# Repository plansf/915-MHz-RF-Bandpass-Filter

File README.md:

# RF915: 915 MHz LC Filter

I’m developing this as a student RF hardware project: design a compact filter for
the 902–928 MHz band, model it, lay out a PCB, then compare the model with a
NanoVNA measurement. Revision A is the digital prototype, the boards have been simulated, but yet to be fabricated and tested to see comparison of real Vs. theoretical measurements.

I’m keeping the assumptions and current limits visible so the simulation is not mistaken for measured hardware results.

## The design

The filter is a passive, three-resonator LC bandpass network with 50-ohm SMA
ports. It uses 1.8 pF series capacitors, 15 nH series inductors, and a 1.8 nH /
10 pF shunt resonator. The KiCad package includes the filter PCB and a separate
through-reference board. Both are routed as two-layer, 40 x 24 mm boards for a
specified 0.8 mm FR4 stackup.

The Python model calculates S-parameters and can analyze Touchstone 1.x `.s2p`
files. It includes a typical vendor model for the inductors and estimates for
capacitor, trace, connector, and ground-return parasitics. Those PCB and launch
values are assumptions; the design has not had full-wave EM analysis.

## Current results

The simulated board model meets the initial targets in `design.json`:

| Measure | Target | Estimated board model |
|---|---:|---:|
| Insertion loss across 902–928 MHz | ≤ 3 dB | 1.01 dB worst case |
| Return loss across 902–928 MHz | ≥ 10 dB | 25.14 dB worst case |
| Attenuation at 433 MHz | ≥ 15 dB | 30.44 dB |
| Attenuation at 1830 MHz | ≥ 15 dB | 47.65 dB |

These are simulation outputs, not acceptance results. The ideal lumped model
misses the return-loss target, which shows how much the prediction depends on
the estimated PCB parasitics. In an illustrative 300-case sensitivity sweep,
275 cases met the modeled targets; this is not a manufacturing-yield estimate.
See `results/simulation/metrics.json` and `results/simulation/response.png`.

## What has been checked

The original validation run recorded 10 Python tests passing, clean KiCad ERC
and DRC checks for both boards, and valid fabrication exports. These checks cover
the digital design package. The included KiCad reports are the raw ERC/DRC
outputs. No board has been ordered, assembled, or tested with a VNA. The design
also has not had production qualification or full-wave EM analysis.

## Run the model

Python 3.11+ with NumPy and Matplotlib is needed for the analysis scripts. From
this folder in PowerShell:

```powershell
python -m venv .venv
.\.venv\Scripts\python.exe -m pip install -r requirements.txt
.\.venv\Scripts\python.exe rf915.py simulate
```

To analyze a real acquisition, keep the original Touchstone file and complete
`measurements/metadata-template.json` with the instrument and calibration
details. Then run:

```powershell
.\.venv\Scripts\python.exe rf915.py analyze measurements\filter-revA.s2p --kind measured --metadata measurements\filter-revA.json --output results\measured-revA --reference results\simulation\nominal.s2p
```

The analyzer requires complete coverage of the passband and will not label the
included simulated files as measured data. It reports S-parameter metrics, a
comparison plot, CSV data, and group delay.

## Next step: build and measure

The Gerber archives are in `fabrication/`; the parts list is `hardware/BOM.csv`.
Before ordering, confirm the fabricator can provide the specified two-layer,
0.8 mm FR4 stackup. Assemble the filter and through-reference boards, check them
with a multimeter, calibrate the NanoVNA at the cable ends, and save the raw
Touchstone exports and measurement metadata. Compare those measurements with
the model before deciding whether to tune or make Revision B. Do not substitute
1.6 mm board thickness without revising the design.

## Repository map

- `hardware/` — editable KiCad design, BOM, and ERC/DRC records
- `fabrication/` — Gerber, drill, and board ZIP files
- `rf915.py`, `design.json` — model, Touchstone analysis, and design inputs
- `results/simulation/` — simulated Touchstone files, metrics, and plots
- `measurements/` — metadata template and place for future raw measurements
- `tests/` — model and Touchstone parser tests

## References

- [Coilcraft 0603HP SPICE model](https://www.coilcraft.com/getmedia/353e55d2-1d20-470a-9567-550d989b0e5d/spice_0603hp.pdf) — inductor model basis.
- [Amphenol 132134 mechanical drawing](https://www.amphenolrf.com/library/download/link/link_id/593003/parent/132134/) — vertical SMA footprint dimensions.
- [KiCad 9 CLI documentation](https://docs.kicad.org/9.0/en/cli/cli.html) — ERC, DRC, and fabrication export tools.
- [NanoVNA calibration](https://nanovna.com/?page_id=2) and [NanoVNA-Saver](https://github.com/NanoVNA-Saver/nanovna-saver) — instrument setup and Touchstone export references.

The vendor datasheet and KiCad-derived footprints retain their original sources;
they are included as references and are not claimed as original work.

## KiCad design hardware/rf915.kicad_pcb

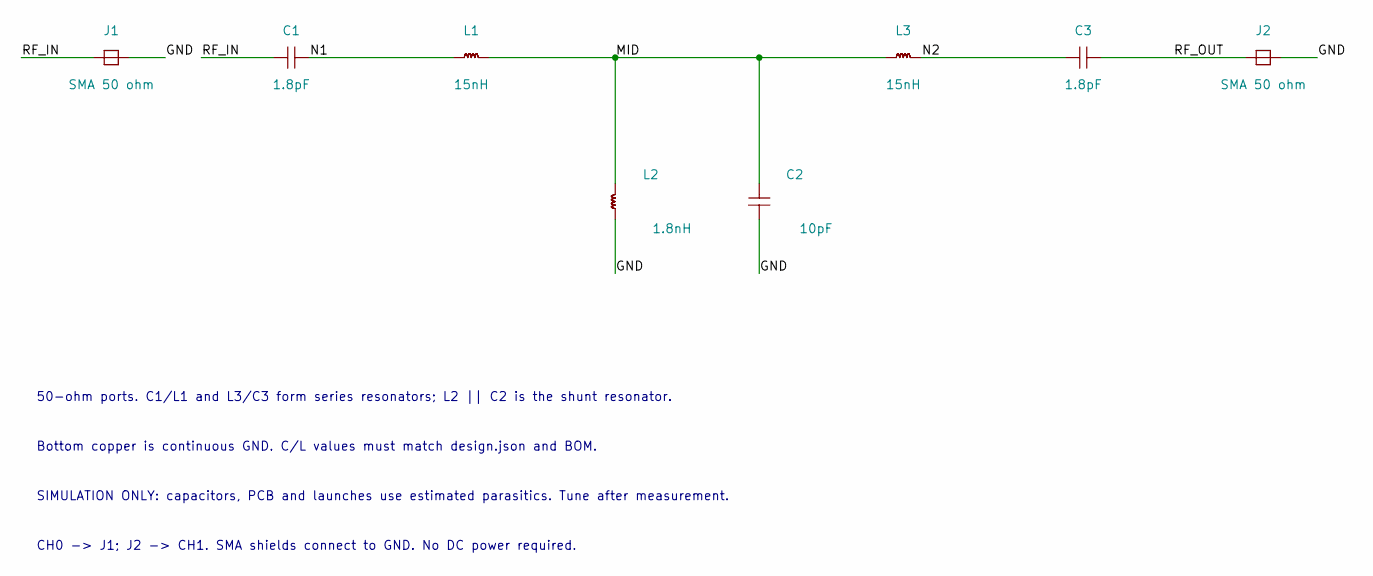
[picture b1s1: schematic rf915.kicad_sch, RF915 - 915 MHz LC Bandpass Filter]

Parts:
C1, C3: 1.8pF; C_0402_1005Metric
C2: 10pF; C_0402_1005Metric
J1, J2: SMA 50 ohm; SMA_Amphenol_132134_Vertical
L1, L3: 15nH; L_0603_1608Metric
L2: 1.8nH; L_0603_1608Metric

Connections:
/GND: C2.1, J1.2, J2.2, L2.1
/MID: C2.2, L1.2, L2.2, L3.1
/N1: C1.2, L1.1
/N2: C3.1, L3.2
/RF_IN: C1.1, J1.1
/RF_OUT: C3.2, J2.1

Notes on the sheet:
50-ohm ports. C1/L1 and L3/C3 form series resonators; L2 || C2 is the shunt resonator.
Bottom copper is continuous GND. C/L values must match design.json and BOM.
SIMULATION ONLY: capacitors, PCB and launches use estimated parasitics. Tune after measurement.
CH0 -> J1; J2 -> CH1. SMA shields connect to GND. No DC power required.

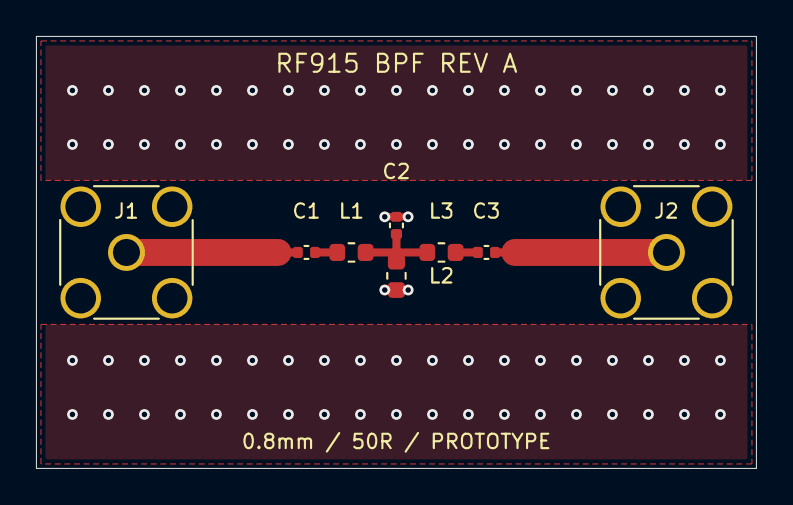
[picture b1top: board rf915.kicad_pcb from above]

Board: 2 copper layers, 40.0 x 24.0 mm, 8 parts (0 on the bottom side), 6 nets.
